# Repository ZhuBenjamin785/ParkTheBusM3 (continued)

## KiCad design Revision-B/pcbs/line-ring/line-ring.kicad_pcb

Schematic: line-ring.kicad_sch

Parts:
C1, C2, C4: 100n 16V; C_0805_2012Metric
C3: 10u 10V; C_0805_2012Metric
J1: REV B LINE LINK; IDC-Header_2x05_P2.54mm_Vertical
Q1, Q2, Q3, Q4, Q5, Q6, Q7, Q8, Q9, Q10, Q11, Q12, Q13, Q14, Q15, Q16, Q17, Q18, Q19, Q20, Q21, Q22, Q23, Q24, Q25, Q26, Q27, Q28, Q29, Q30, Q31, Q32: QRE1113GR; OnSemi_CASE100CY
Q33: AO3400A; SOT-23
R1, R2, R3, R4, R5, R6, R7, R8, R9, R10, R11, R12, R13, R14, R15, R16, R17, R18, R19, R20, R21, R22, R23, R24, R25, R26, R27, R28, R29, R30, R31, R32: 10k 1%; R_0805_2012Metric
R33, R34, R35, R36, R37, R38, R39, R40, R41, R42, R43, R44, R45, R46, R47, R48: 220R 1%; R_0805_2012Metric
R49: 100R; R_0805_2012Metric
R50: 47k; R_0805_2012Metric
R51, R52: 47R; R_0805_2012Metric
U1, U2: CD74HC4067M96; SOIC-24W_7.5x15.4mm_P1.27mm
U3: TLV9062IDR; SOIC-8_3.9x4.9mm_P1.27mm

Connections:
3V3: C1.1, C2.1, C4.1, J1.4 (3V3), R1.2, R2.2, R3.2, R4.2, R5.2, R6.2, R7.2, R8.2, R9.2, R10.2, R11.2, R12.2, R13.2, R14.2, R15.2, R16.2, R17.2, R18.2, R19.2, R20.2, R21.2, R22.2, R23.2, R24.2, R25.2, R26.2, R27.2, R28.2, R29.2, R30.2, R31.2, R32.2, U1.24 (VCC), U2.24 (VCC), U3.8 (V+)
5V: C3.1, J1.10 (5V), R33.1, R34.1, R35.1, R36.1, R37.1, R38.1, R39.1, R40.1, R41.1, R42.1, R43.1, R44.1, R45.1, R46.1, R47.1, R48.1
BUF_A: R51.1, U3.1 (OUTA), U3.2 (INA-)
BUF_B: R52.1, U3.6 (INB-), U3.7 (OUTB)
GND: C1.2, C2.2, C3.2, C4.2, J1.2 (GND), Q1.4 (E), Q2.4 (E), Q3.4 (E), Q4.4 (E), Q5.4 (E), Q6.4 (E), Q7.4 (E), Q8.4 (E), Q9.4 (E), Q10.4 (E), Q11.4 (E), Q12.4 (E), Q13.4 (E), Q14.4 (E), Q15.4 (E), Q16.4 (E), Q17.4 (E), Q18.4 (E), Q19.4 (E), Q20.4 (E), Q21.4 (E), Q22.4 (E), Q23.4 (E), Q24.4 (E), Q25.4 (E), Q26.4 (E), Q27.4 (E), Q28.4 (E), Q29.4 (E), Q30.4 (E), Q31.4 (E), Q32.4 (E), Q33.2 (S), R50.2, U1.12 (GND), U1.15 (EN), U2.12 (GND), U2.15 (EN), U3.4 (V-)
IR_GATE: Q33.1 (G), R49.2, R50.1
IR_RETURN: Q2.2 (K), Q4.2 (K), Q6.2 (K), Q8.2 (K), Q10.2 (K), Q12.2 (K), Q14.2 (K), Q16.2 (K), Q18.2 (K), Q20.2 (K), Q22.2 (K), Q24.2 (K), Q26.2 (K), Q28.2 (K), Q30.2 (K), Q32.2 (K), Q33.3 (D)
LED_0: Q1.1 (A), R33.2
LED_1: Q3.1 (A), R34.2
LED_2: Q5.1 (A), R35.2
LED_3: Q7.1 (A), R36.2
LED_4: Q9.1 (A), R37.2
LED_5: Q11.1 (A), R38.2
LED_6: Q13.1 (A), R39.2
LED_7: Q15.1 (A), R40.2
LED_8: Q17.1 (A), R41.2
LED_9: Q19.1 (A), R42.2
LED_10: Q21.1 (A), R43.2
LED_11: Q23.1 (A), R44.2
LED_12: Q25.1 (A), R45.2
LED_13: Q27.1 (A), R46.2
LED_14: Q29.1 (A), R47.2
LED_15: Q31.1 (A), R48.2
LINE_ANALOG: J1.1 (LINE_ANALOG), R51.2
LINE_B: J1.3 (LINE_B), R52.2
LINE_CTRL: J1.9 (LINE_CTRL), R49.1
LINE_S0: J1.5 (LINE_S0), U1.10 (S0), U2.10 (S0)
LINE_S1: J1.6 (LINE_S1), U1.11 (S1), U2.11 (S1)
LINE_S2: J1.7 (LINE_S2), U1.14 (S2), U2.14 (S2)
LINE_S3: J1.8 (LINE_S3), U1.13 (S3), U2.13 (S3)
MUX_0: U1.1 (COM), U3.3 (INA+)
MUX_1: U2.1 (COM), U3.5 (INB+)
PAIR_0: Q1.2 (K), Q2.1 (A)
PAIR_1: Q3.2 (K), Q4.1 (A)
PAIR_2: Q5.2 (K), Q6.1 (A)
PAIR_3: Q7.2 (K), Q8.1 (A)
PAIR_4: Q9.2 (K), Q10.1 (A)
PAIR_5: Q11.2 (K), Q12.1 (A)
PAIR_6: Q13.2 (K), Q14.1 (A)
PAIR_7: Q15.2 (K), Q16.1 (A)
PAIR_8: Q17.2 (K), Q18.1 (A)
PAIR_9: Q19.2 (K), Q20.1 (A)
PAIR_10: Q21.2 (K), Q22.1 (A)
PAIR_11: Q23.2 (K), Q24.1 (A)
PAIR_12: Q25.2 (K), Q26.1 (A)
PAIR_13: Q27.2 (K), Q28.1 (A)
PAIR_14: Q29.2 (K), Q30.1 (A)
PAIR_15: Q31.2 (K), Q32.1 (A)
SENSE_0: Q1.3 (C), R1.1, U1.9 (I0)
SENSE_1: Q2.3 (C), R2.1, U2.9 (I0)
SENSE_2: Q3.3 (C), R3.1, U1.8 (I1)
SENSE_3: Q4.3 (C), R4.1, U2.8 (I1)
SENSE_4: Q5.3 (C), R5.1, U1.7 (I2)
SENSE_5: Q6.3 (C), R6.1, U2.7 (I2)
SENSE_6: Q7.3 (C), R7.1, U1.6 (I3)
SENSE_7: Q8.3 (C), R8.1, U2.6 (I3)
SENSE_8: Q9.3 (C), R9.1, U1.5 (I4)
SENSE_9: Q10.3 (C), R10.1, U2.5 (I4)
SENSE_10: Q11.3 (C), R11.1, U1.4 (I5)
SENSE_11: Q12.3 (C), R12.1, U2.4 (I5)
SENSE_12: Q13.3 (C), R13.1, U1.3 (I6)
SENSE_13: Q14.3 (C), R14.1, U2.3 (I6)
SENSE_14: Q15.3 (C), R15.1, U1.2 (I7)
SENSE_15: Q16.3 (C), R16.1, U2.2 (I7)
SENSE_16: Q17.3 (C), R17.1, U1.23 (I8)
SENSE_17: Q18.3 (C), R18.1, U2.23 (I8)
SENSE_18: Q19.3 (C), R19.1, U1.22 (I9)
SENSE_19: Q20.3 (C), R20.1, U2.22 (I9)
SENSE_20: Q21.3 (C), R21.1, U1.21 (I10)
SENSE_21: Q22.3 (C), R22.1, U2.21 (I10)
SENSE_22: Q23.3 (C), R23.1, U1.20 (I11)
SENSE_23: Q24.3 (C), R24.1, U2.20 (I11)
SENSE_24: Q25.3 (C), R25.1, U1.19 (I12)
SENSE_25: Q26.3 (C), R26.1, U2.19 (I12)
SENSE_26: Q27.3 (C), R27.1, U1.18 (I13)
SENSE_27: Q28.3 (C), R28.1, U2.18 (I13)
SENSE_28: Q29.3 (C), R29.1, U1.17 (I14)
SENSE_29: Q30.3 (C), R30.1, U2.17 (I14)
SENSE_30: Q31.3 (C), R31.1, U1.16 (I15)
SENSE_31: Q32.3 (C), R32.1, U2.16 (I15)

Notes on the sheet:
Controller ribbon and emitter switch
Even and odd acquisition banks
Address 00 / even and odd optical channels
Address 01 / even and odd optical channels
Address 02 / even and odd optical channels
Address 03 / even and odd optical channels
Address 04 / even and odd optical channels
Address 05 / even and odd optical channels
Address 06 / even and odd optical channels
Address 07 / even and odd optical channels
Address 08 / even and odd optical channels
Address 09 / even and odd optical channels
Address 10 / even and odd optical channels
Address 11 / even and odd optical channels
Address 12 / even and odd optical channels
Address 13 / even and odd optical channels
Address 14 / even and odd optical channels
Address 15 / even and odd optical channels

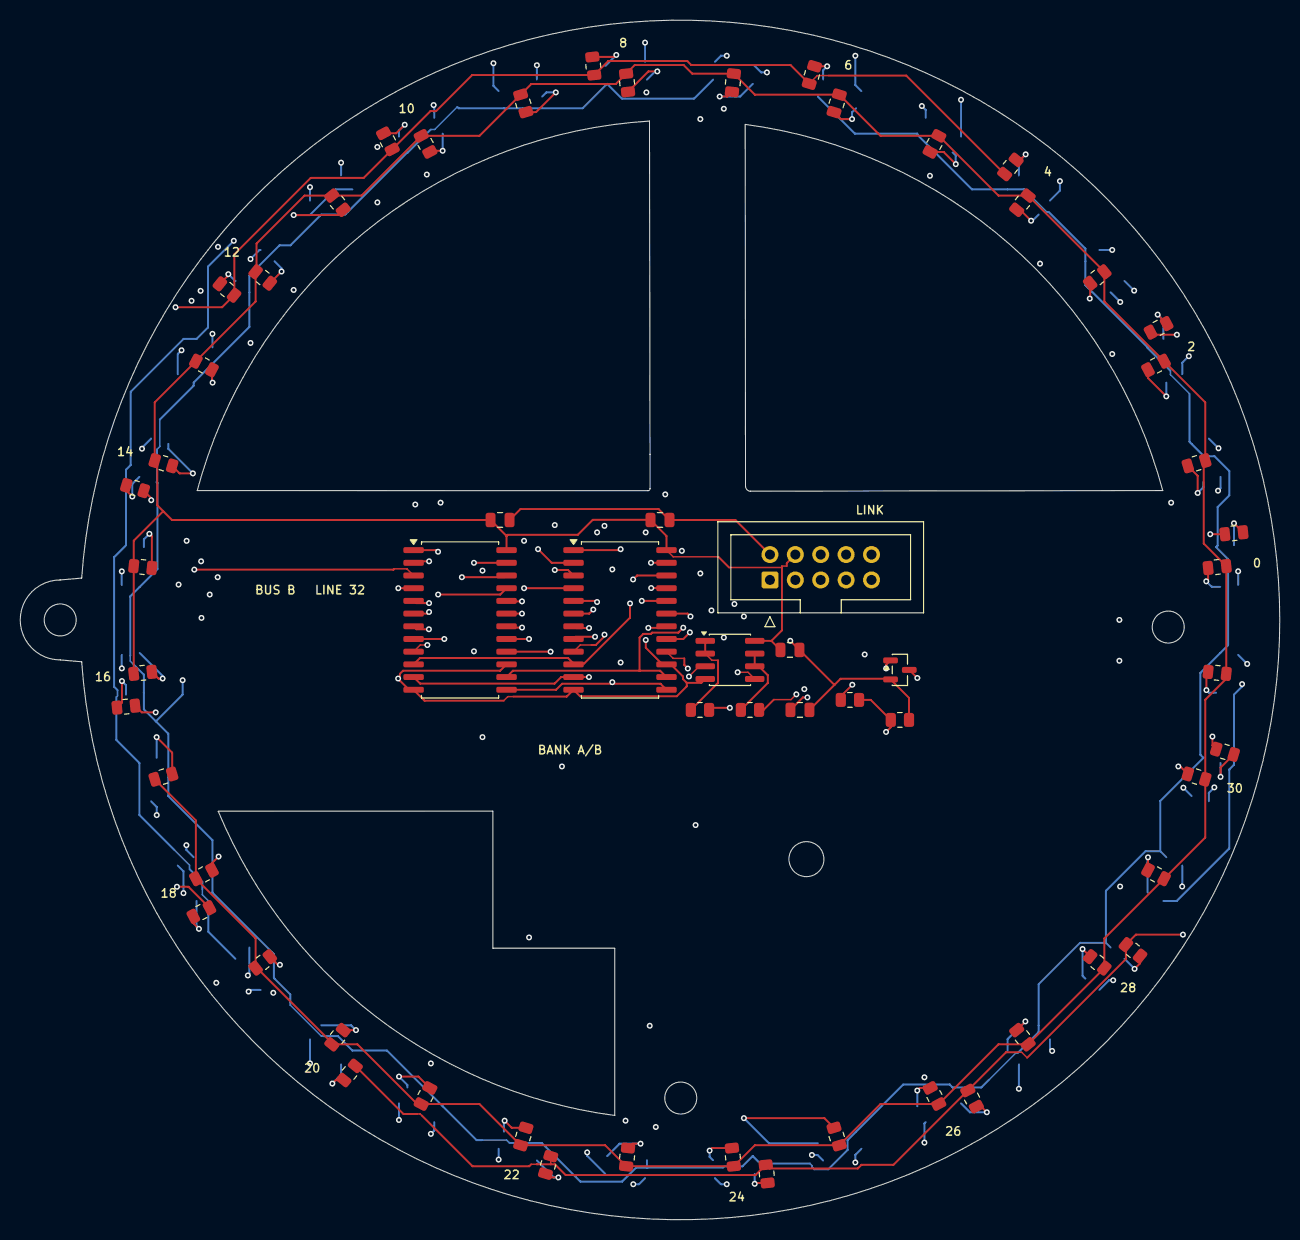
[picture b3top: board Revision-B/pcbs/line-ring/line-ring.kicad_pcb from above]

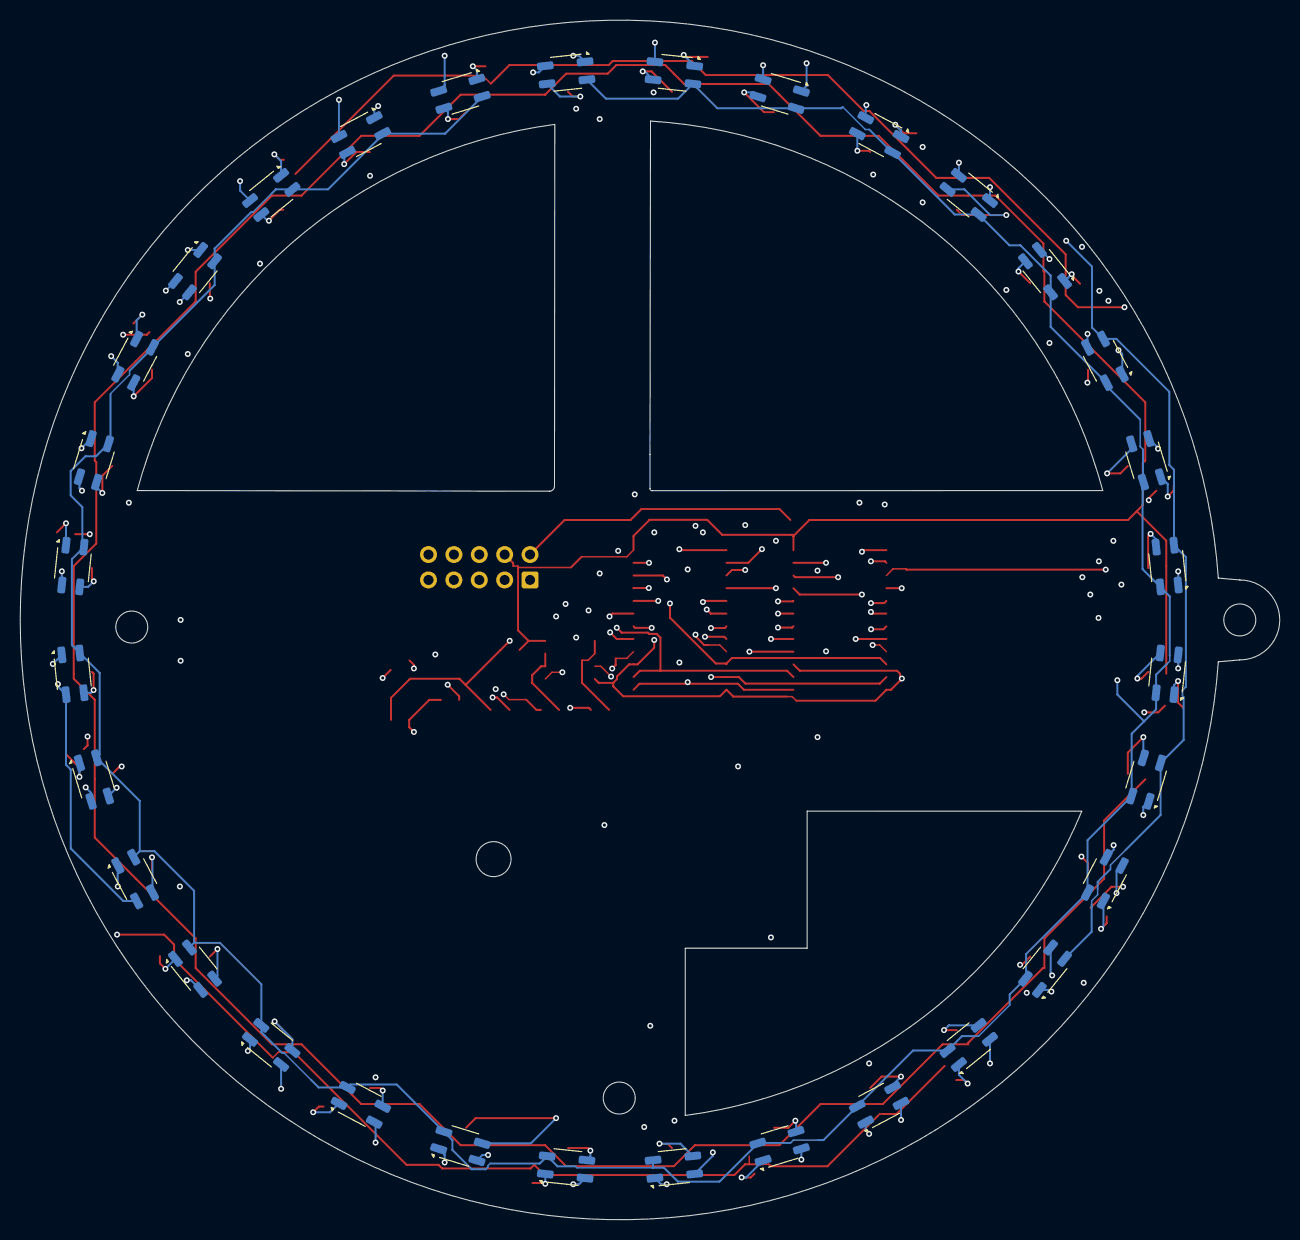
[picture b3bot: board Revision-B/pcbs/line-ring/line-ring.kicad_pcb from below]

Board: 4 copper layers, 126.0 x 120.0 mm, 97 parts (32 on the bottom side), 80 nets.

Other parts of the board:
H1, H2, H3: NPTH 3.2
H4: NPTH 3.5

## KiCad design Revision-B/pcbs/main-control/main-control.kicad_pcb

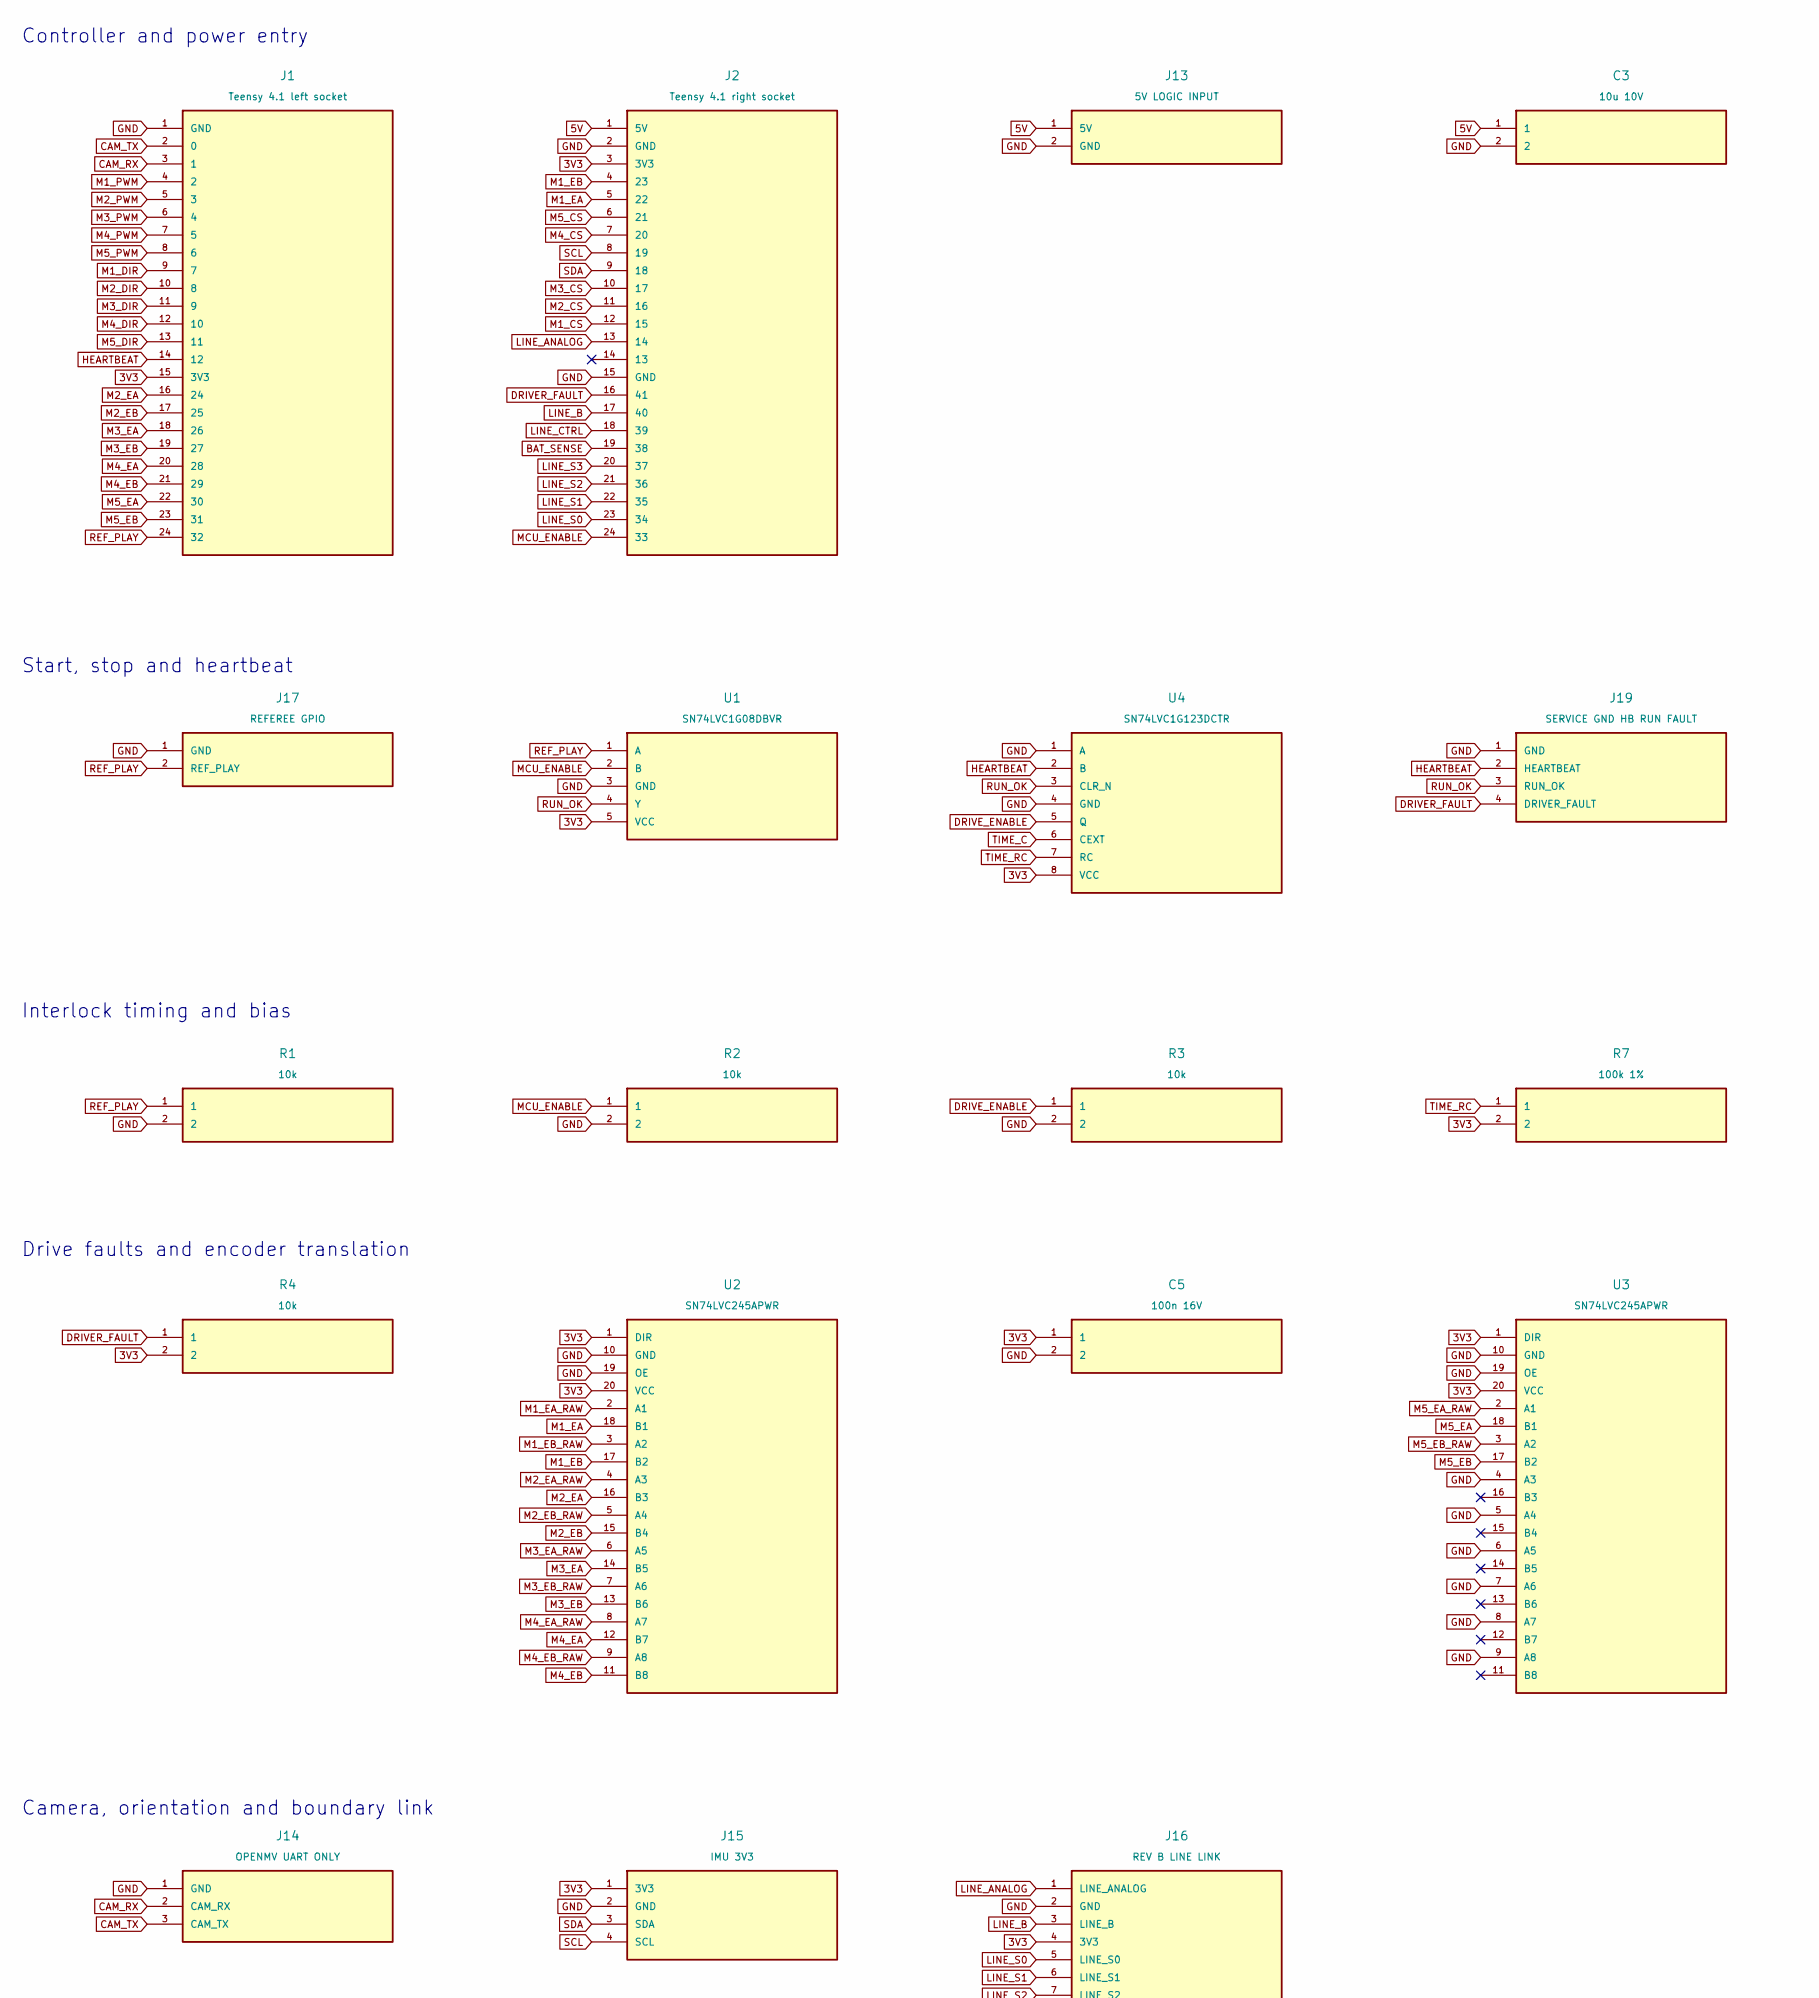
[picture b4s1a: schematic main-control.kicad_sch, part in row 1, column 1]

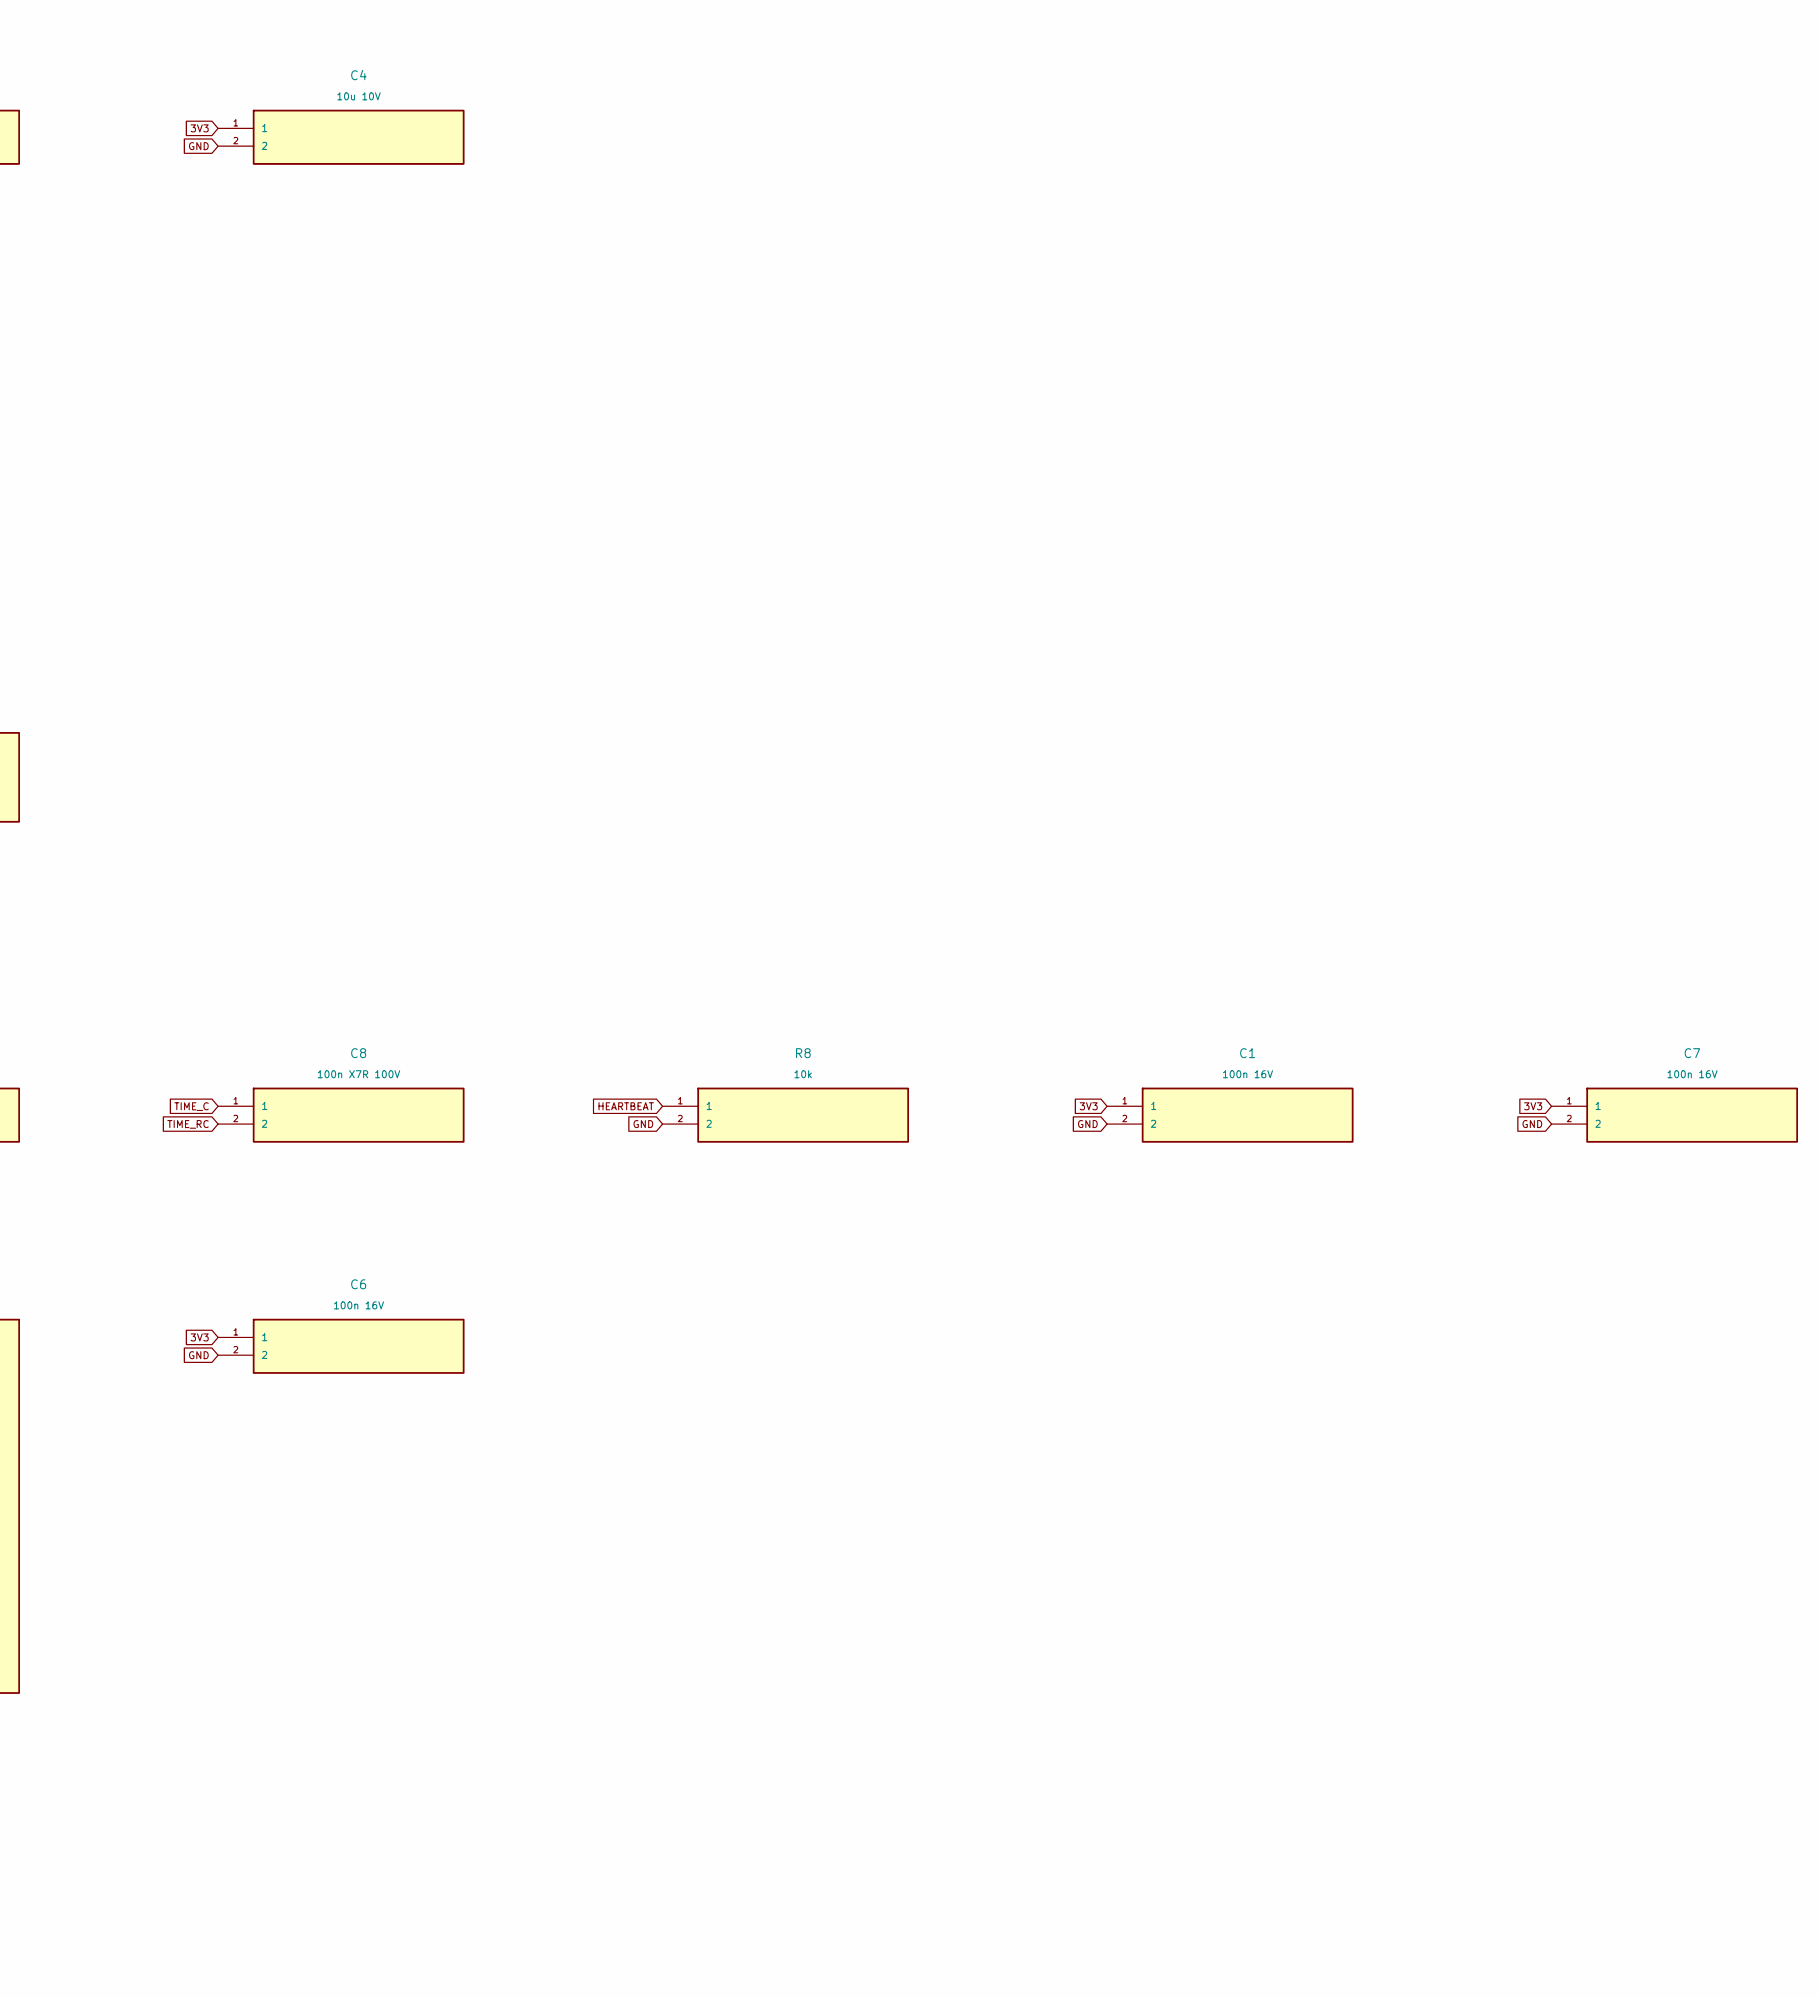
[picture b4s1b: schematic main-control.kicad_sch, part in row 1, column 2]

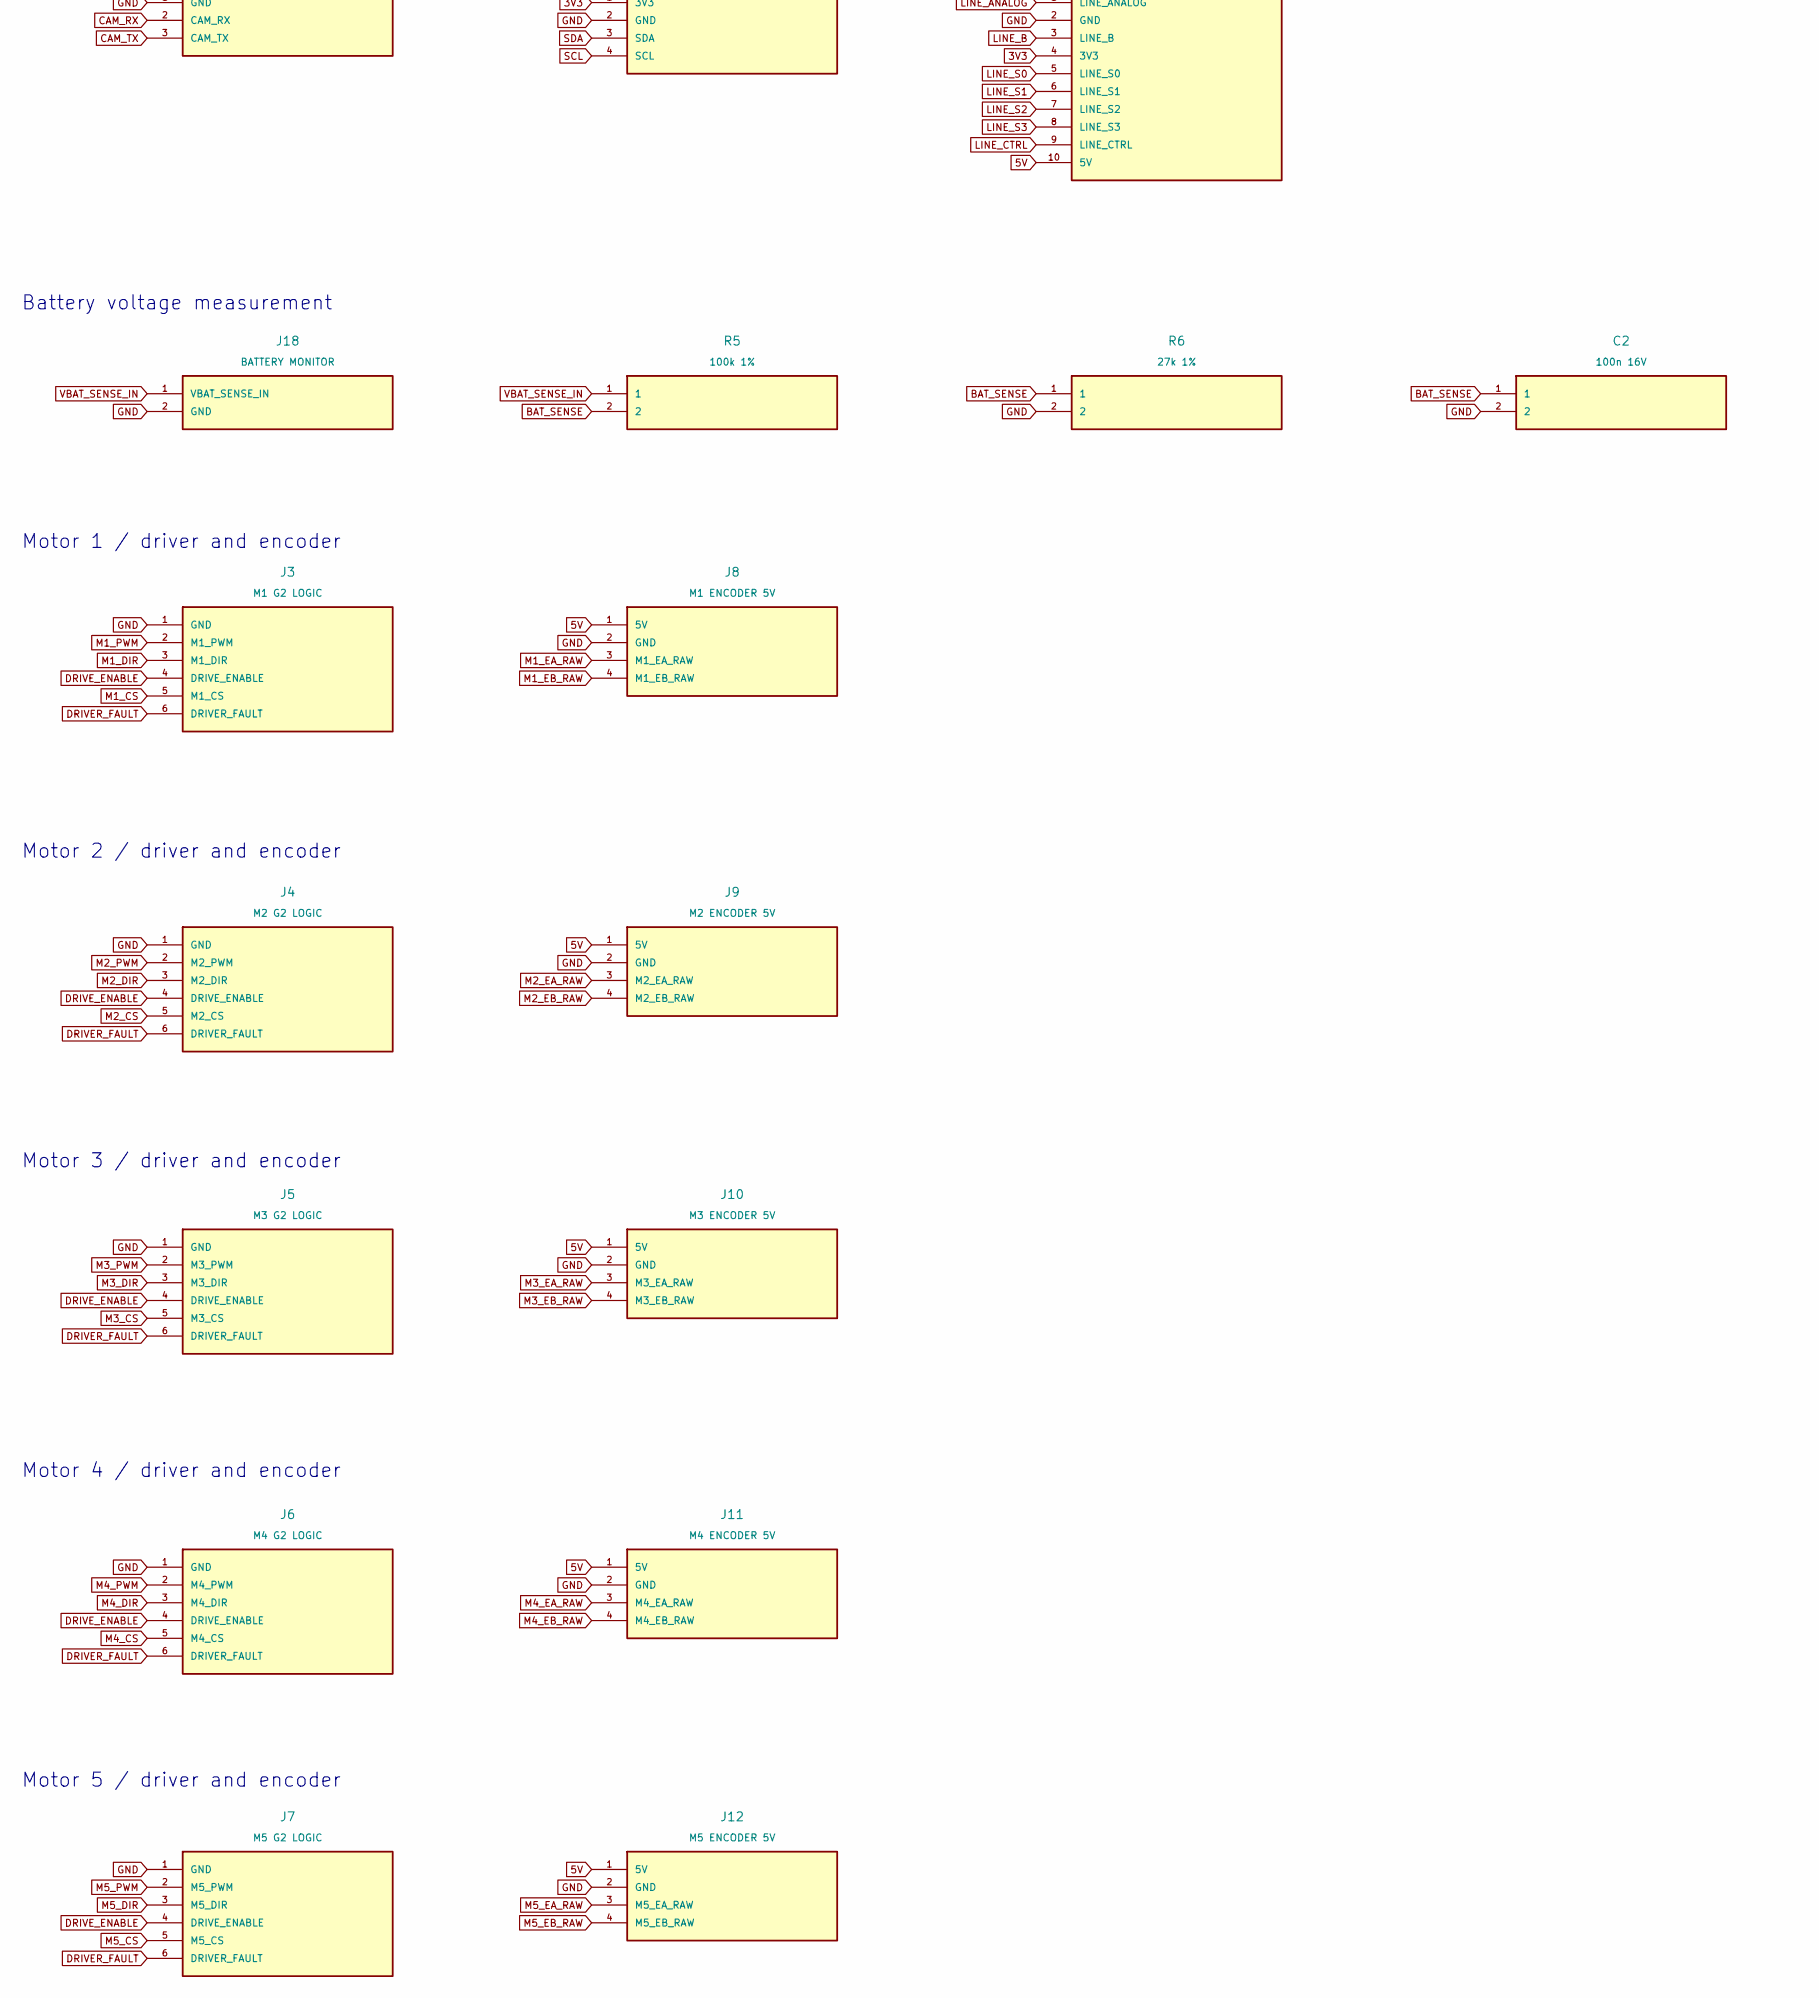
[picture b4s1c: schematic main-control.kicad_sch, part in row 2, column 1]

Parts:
C1, C2, C5, C6, C7: 100n 16V; C_0805_2012Metric
C3, C4: 10u 10V; C_0805_2012Metric
C8: 100n X7R 100V; C_0805_2012Metric
J1: Teensy 4.1 left socket; PinSocket_1x24_P2.54mm_Vertical
J2: Teensy 4.1 right socket; PinSocket_1x24_P2.54mm_Vertical
J3: M1 G2 LOGIC; JST_XH_B6B-XH-A_1x06_P2.50mm_Vertical
J4: M2 G2 LOGIC; JST_XH_B6B-XH-A_1x06_P2.50mm_Vertical
J5: M3 G2 LOGIC; JST_XH_B6B-XH-A_1x06_P2.50mm_Vertical
J6: M4 G2 LOGIC; JST_XH_B6B-XH-A_1x06_P2.50mm_Vertical
J7: M5 G2 LOGIC; JST_XH_B6B-XH-A_1x06_P2.50mm_Vertical
J8: M1 ENCODER 5V; JST_XH_B4B-XH-A_1x04_P2.50mm_Vertical
J9: M2 ENCODER 5V; JST_XH_B4B-XH-A_1x04_P2.50mm_Vertical
J10: M3 ENCODER 5V; JST_XH_B4B-XH-A_1x04_P2.50mm_Vertical
J11: M4 ENCODER 5V; JST_XH_B4B-XH-A_1x04_P2.50mm_Vertical
J12: M5 ENCODER 5V; JST_XH_B4B-XH-A_1x04_P2.50mm_Vertical
J13: 5V LOGIC INPUT; JST_XH_B2B-XH-A_1x02_P2.50mm_Vertical
J14: OPENMV UART ONLY; JST_XH_B3B-XH-A_1x03_P2.50mm_Vertical
J15: IMU 3V3; JST_XH_B4B-XH-A_1x04_P2.50mm_Vertical
J16: REV B LINE LINK; IDC-Header_2x05_P2.54mm_Vertical
J17: REFEREE GPIO; JST_XH_B2B-XH-A_1x02_P2.50mm_Vertical
J18: BATTERY MONITOR; JST_XH_B2B-XH-A_1x02_P2.50mm_Vertical
J19: SERVICE GND HB RUN FAULT; JST_XH_B4B-XH-A_1x04_P2.50mm_Vertical
R1, R2, R3, R4, R8: 10k; R_0805_2012Metric
R5, R7: 100k 1%; R_0805_2012Metric
R6: 27k 1%; R_0805_2012Metric
U1: SN74LVC1G08DBVR; SOT-23-5
U2, U3: SN74LVC245APWR; TSSOP-20_4.4x6.5mm_P0.65mm
U4: SN74LVC1G123DCTR; SSOP-8_2.95x2.8mm_P0.65mm

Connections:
3V3: C1.1, C4.1, C5.1, C6.1, C7.1, J1.15 (3V3), J2.3 (3V3), J15.1 (3V3), J16.4 (3V3), R4.2, R7.2, U1.5 (VCC), U2.1 (DIR), U2.20 (VCC), U3.1 (DIR), U3.20 (VCC), U4.8 (VCC)
5V: C3.1, J2.1 (5V), J8.1 (5V), J9.1 (5V), J10.1 (5V), J11.1 (5V), J12.1 (5V), J13.1 (5V), J16.10 (5V)
BAT_SENSE: C2.1, J2.19 (38), R5.2, R6.1
CAM_RX: J1.3 (1), J14.2 (CAM_RX)
CAM_TX: J1.2 (0), J14.3 (CAM_TX)
DRIVER_FAULT: J2.16 (41), J3.6 (DRIVER_FAULT), J4.6 (DRIVER_FAULT), J5.6 (DRIVER_FAULT), J6.6 (DRIVER_FAULT), J7.6 (DRIVER_FAULT), J19.4 (DRIVER_FAULT), R4.1
DRIVE_ENABLE: J3.4 (DRIVE_ENABLE), J4.4 (DRIVE_ENABLE), J5.4 (DRIVE_ENABLE), J6.4 (DRIVE_ENABLE), J7.4 (DRIVE_ENABLE), R3.1, U4.5 (Q)
GND: C1.2, C2.2, C3.2, C4.2, C5.2, C6.2, C7.2, J1.1 (GND), J2.2 (GND), J2.15 (GND), J3.1 (GND), J4.1 (GND), J5.1 (GND), J6.1 (GND), J7.1 (GND), J8.2 (GND), J9.2 (GND), J10.2 (GND), J11.2 (GND), J12.2 (GND), J13.2 (GND), J14.1 (GND), J15.2 (GND), J16.2 (GND), J17.1 (GND), J18.2 (GND), J19.1 (GND), R1.2, R2.2, R3.2, R6.2, R8.2, U1.3 (GND), U2.10 (GND), U2.19 (OE), U3.4 (A3), U3.5 (A4), U3.6 (A5), U3.7 (A6), U3.8 (A7), U3.9 (A8), U3.10 (GND), U3.19 (OE), U4.1 (A), U4.4 (GND)
HEARTBEAT: J1.14 (12), J19.2 (HEARTBEAT), R8.1, U4.2 (B)
LINE_ANALOG: J2.13 (14), J16.1 (LINE_ANALOG)
LINE_B: J2.17 (40), J16.3 (LINE_B)
LINE_CTRL: J2.18 (39), J16.9 (LINE_CTRL)
LINE_S0: J2.23 (34), J16.5 (LINE_S0)
LINE_S1: J2.22 (35), J16.6 (LINE_S1)
LINE_S2: J2.21 (36), J16.7 (LINE_S2)
LINE_S3: J2.20 (37), J16.8 (LINE_S3)
M1_CS: J2.12 (15), J3.5 (M1_CS)
M1_DIR: J1.9 (7), J3.3 (M1_DIR)
M1_EA: J2.5 (22), U2.18 (B1)
M1_EA_RAW: J8.3 (M1_EA_RAW), U2.2 (A1)
M1_EB: J2.4 (23), U2.17 (B2)
M1_EB_RAW: J8.4 (M1_EB_RAW), U2.3 (A2)
M1_PWM: J1.4 (2), J3.2 (M1_PWM)
M2_CS: J2.11 (16), J4.5 (M2_CS)
M2_DIR: J1.10 (8), J4.3 (M2_DIR)
M2_EA: J1.16 (24), U2.16 (B3)
M2_EA_RAW: J9.3 (M2_EA_RAW), U2.4 (A3)
M2_EB: J1.17 (25), U2.15 (B4)
M2_EB_RAW: J9.4 (M2_EB_RAW), U2.5 (A4)
M2_PWM: J1.5 (3), J4.2 (M2_PWM)
M3_CS: J2.10 (17), J5.5 (M3_CS)
M3_DIR: J1.11 (9), J5.3 (M3_DIR)
M3_EA: J1.18 (26), U2.14 (B5)
M3_EA_RAW: J10.3 (M3_EA_RAW), U2.6 (A5)
M3_EB: J1.19 (27), U2.13 (B6)
M3_EB_RAW: J10.4 (M3_EB_RAW), U2.7 (A6)
M3_PWM: J1.6 (4), J5.2 (M3_PWM)
M4_CS: J2.7 (20), J6.5 (M4_CS)
M4_DIR: J1.12 (10), J6.3 (M4_DIR)
M4_EA: J1.20 (28), U2.12 (B7)
M4_EA_RAW: J11.3 (M4_EA_RAW), U2.8 (A7)
M4_EB: J1.21 (29), U2.11 (B8)
M4_EB_RAW: J11.4 (M4_EB_RAW), U2.9 (A8)
M4_PWM: J1.7 (5), J6.2 (M4_PWM)
M5_CS: J2.6 (21), J7.5 (M5_CS)
M5_DIR: J1.13 (11), J7.3 (M5_DIR)
M5_EA: J1.22 (30), U3.18 (B1)
M5_EA_RAW: J12.3 (M5_EA_RAW), U3.2 (A1)
M5_EB: J1.23 (31), U3.17 (B2)
M5_EB_RAW: J12.4 (M5_EB_RAW), U3.3 (A2)
M5_PWM: J1.8 (6), J7.2 (M5_PWM)
MCU_ENABLE: J2.24 (33), R2.1, U1.2 (B)
REF_PLAY: J1.24 (32), J17.2 (REF_PLAY), R1.1, U1.1 (A)
RUN_OK: J19.3 (RUN_OK), U1.4 (Y), U4.3 (CLR_N)
SCL: J2.8 (19), J15.4 (SCL)
SDA: J2.9 (18), J15.3 (SDA)
TIME_C: C8.1, U4.6 (CEXT)
TIME_RC: C8.2, R7.1, U4.7 (RC)
VBAT_SENSE_IN: J18.1 (VBAT_SENSE_IN), R5.1

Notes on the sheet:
Controller and power entry
Start, stop and heartbeat
Interlock timing and bias
Drive faults and encoder translation
Camera, orientation and boundary link
Battery voltage measurement
Motor 1 / driver and encoder
Motor 2 / driver and encoder
Motor 3 / driver and encoder
Motor 4 / driver and encoder
Motor 5 / driver and encoder
